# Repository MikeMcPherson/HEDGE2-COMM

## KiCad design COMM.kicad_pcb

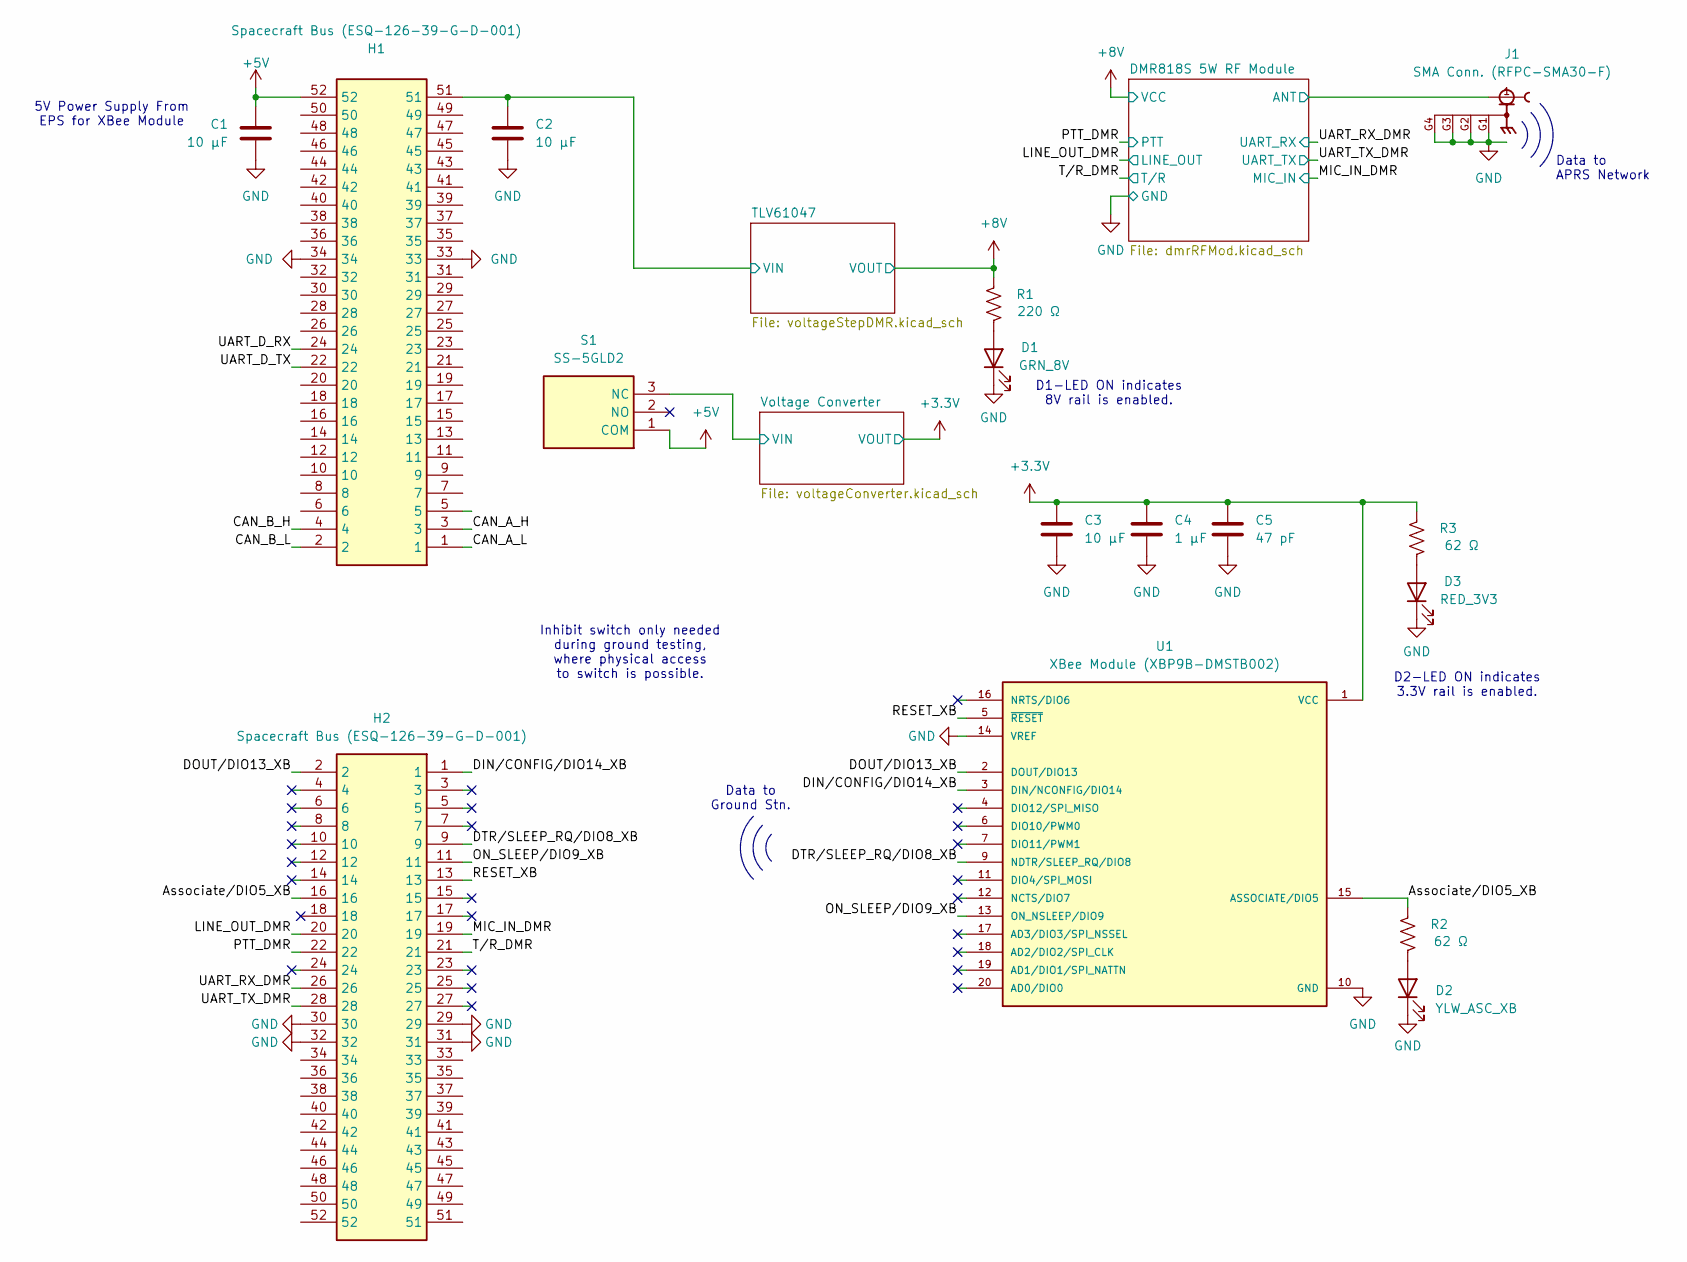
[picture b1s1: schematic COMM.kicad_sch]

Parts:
C1, C2, C3: 10 μF; CAPC1005X70N
C4: 1 μF; CAPC1005X55N
C5: 47 pF; CAPC1005X55N
D1: GRN_8V; LED_D5.0mm
D2: YLW_ASC_XB; LED_D5.0mm
D3: RED_3V3; LED_D5.0mm
H1, H2: Spacecraft Bus (ESQ-126-39-G-D-001); RHDR52W64P254_2X26_6654X495X1135P; Manufacturer_Part_Number ESQ-126-39-G-D-001; Mouser Part Number 200-ESQ12639GD001
J1: SMA Conn. (RFPC-SMA30-F); GRADCONN_RFPC-SMA30-F; PARTREV 1.0
R1: 220 Ω; R_0603_1608Metric
R2, R3: 62 Ω; R_0603_1608Metric
S1: SS-5GLD2; SS5GLD2; Manufacturer_Part_Number SS-5GLD2; Mouser Part Number 653-SS-5GLD2
U1: XBee Module (XBP9B-DMSTB002); DIP2200W51P200L3294H279Q20P

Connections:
+3.3V: C3.1, C4.1, C5.1, R3.2, U1.1 (VCC); also elsewhere on the board
+5V: C1.1, H1.52, S1.1 (COM)
+8V: R1.2; also elsewhere on the board
/Associate/DIO5_XB: H2.16, R2.2, U1.15 (ASSOCIATE/DIO5)
/CAN_A_H: H1.3
/CAN_A_L: H1.1
/CAN_B_H: H1.4
/CAN_B_L: H1.2
/DIN/CONFIG/DIO14_XB: H2.1, U1.3 (DIN/NCONFIG/DIO14)
/DMR818S 5W RF Module/ANT: J1.1; also elsewhere on the board
/DOUT/DIO13_XB: H2.2, U1.2 (DOUT/DIO13)
/DTR/SLEEP_RQ/DIO8_XB: H2.9, U1.9 (NDTR/SLEEP_RQ/DIO8)
/LINE_OUT_DMR: H2.20; also elsewhere on the board
/MIC_IN_DMR: H2.19; also elsewhere on the board
/ON_SLEEP/DIO9_XB: H2.11, U1.13 (ON_NSLEEP/DIO9)
/PTT_DMR: H2.22; also elsewhere on the board
/RESET_XB: H2.13, U1.5 (~RESET)
/TLV61047/VIN: C2.1, H1.51; also elsewhere on the board
/T/R_DMR: H2.21; also elsewhere on the board
/UART_D_RX: H1.24
/UART_D_TX: H1.22
/UART_RX_DMR: H2.26; also elsewhere on the board
/UART_TX_DMR: H2.28; also elsewhere on the board
/Voltage Converter/VIN: S1.3 (NC); also elsewhere on the board
GND: C1.2, C2.2, C3.2, C4.2, C5.2, D1.1 (K), D2.1 (K), D3.1 (K), H1.33, H1.34, H2.29, H2.30, H2.31, H2.32, J1.G1, J1.G2, J1.G3, J1.G4, U1.10 (GND), U1.14 (VREF); also elsewhere on the board
unnamed: D1.2 (A), R1.1
unnamed: D2.2 (A), R2.1
unnamed: D3.2 (A), R3.1

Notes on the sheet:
Data to APRS Network
Inhibit switch only needed during ground testing, where physical access to switch is possible.
5V Power Supply From EPS for XBee Module
Data to Ground Stn.
D1-LED ON indicates 8V rail is enabled.
D2-LED ON indicates 3.3V rail is enabled.

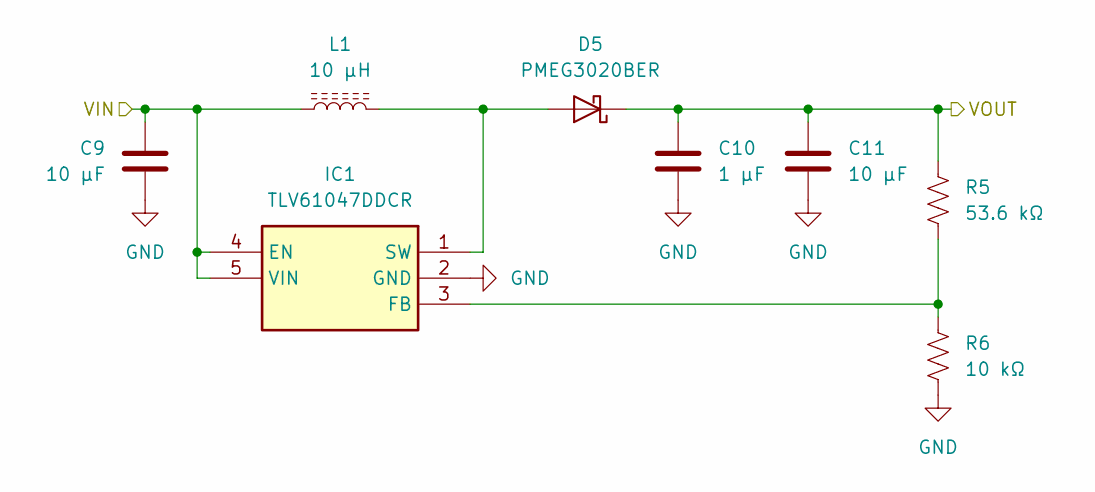
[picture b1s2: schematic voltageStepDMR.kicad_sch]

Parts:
C9, C11: 10 μF; CAPC1005X70N
C10: 1 μF; CAPC1005X55N
D5: PMEG3020BER; DIODE_SOD123W_1P9X2P8_NEX
IC1: TLV61047DDCR; SOT95P280X110-5N; Manufacturer_Part_Number TLV61047DDCR
L1: 10 μH; IND_XAL4040-103MEC
R5: 53.6 kΩ; RESC1608X55N
R6: 10 kΩ; RESC1005X40N

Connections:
+8V: C10.1, C11.1, D5.1 (K), R5.1; also elsewhere on the board
/TLV61047/VIN: C9.1, IC1.4 (EN), IC1.5 (VIN), L1.1; also elsewhere on the board
GND: C9.2, C10.2, C11.2, IC1.2 (GND), R6.2; also elsewhere on the board
unnamed: D5.2 (A), IC1.1 (SW), L1.2
unnamed: IC1.3 (FB), R5.2, R6.1

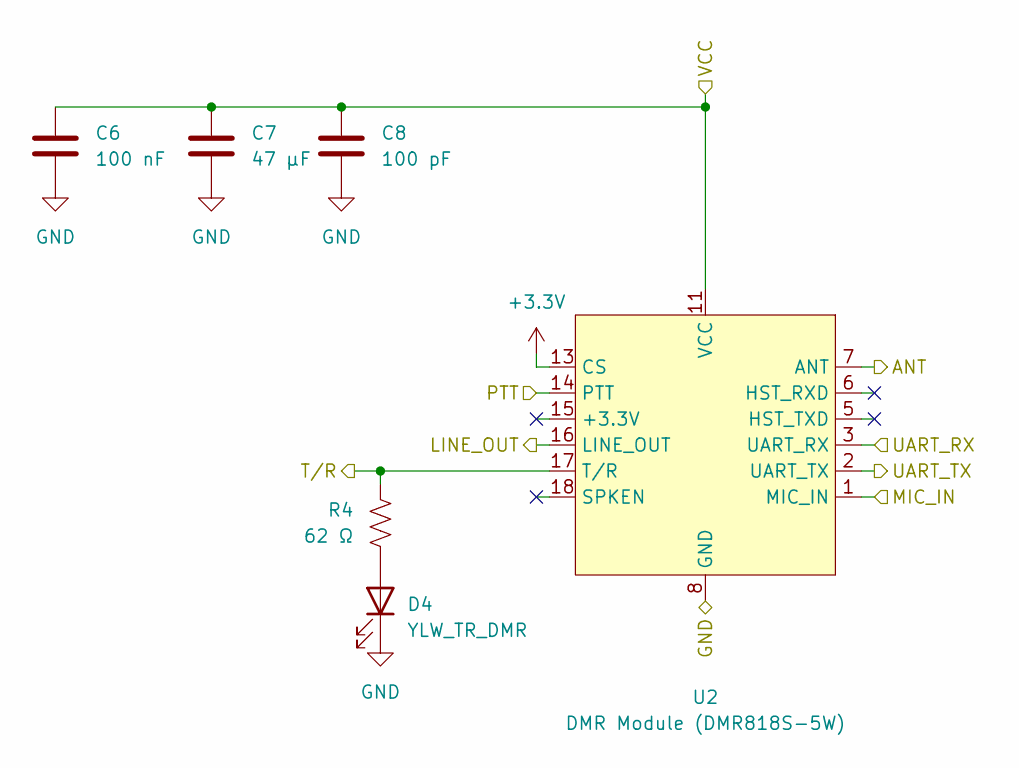
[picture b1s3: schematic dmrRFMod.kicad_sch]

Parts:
C6: 100 nF; CAPC1608X90
C7: 47 μF; CAPC2012X135N
C8: 100 pF; CAPC1005X55N
D4: YLW_TR_DMR; LED_D5.0mm
R4: 62 Ω; R_0603_1608Metric
U2: DMR Module (DMR818S-5W); DMR818S-5W

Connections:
+3.3V: U2.13 (CS); also elsewhere on the board
+8V: C6.1, C7.1, C8.1, U2.11 (VCC); also elsewhere on the board
/DMR818S 5W RF Module/ANT: U2.7 (ANT); also elsewhere on the board
/LINE_OUT_DMR: U2.16 (LINE_OUT); also elsewhere on the board
/MIC_IN_DMR: U2.1 (MIC_IN); also elsewhere on the board
/PTT_DMR: U2.14 (PTT); also elsewhere on the board
/T/R_DMR: R4.1, U2.17 (T/R); also elsewhere on the board
/UART_RX_DMR: U2.3 (UART_RX); also elsewhere on the board
/UART_TX_DMR: U2.2 (UART_TX); also elsewhere on the board
GND: C6.2, C7.2, C8.2, D4.1 (K), U2.8 (GND), U2.9 (GND), U2.10 (GND), U2.19 (GND), U2.20 (GND), U2.21 (GND); also elsewhere on the board
unnamed: D4.2 (A), R4.2

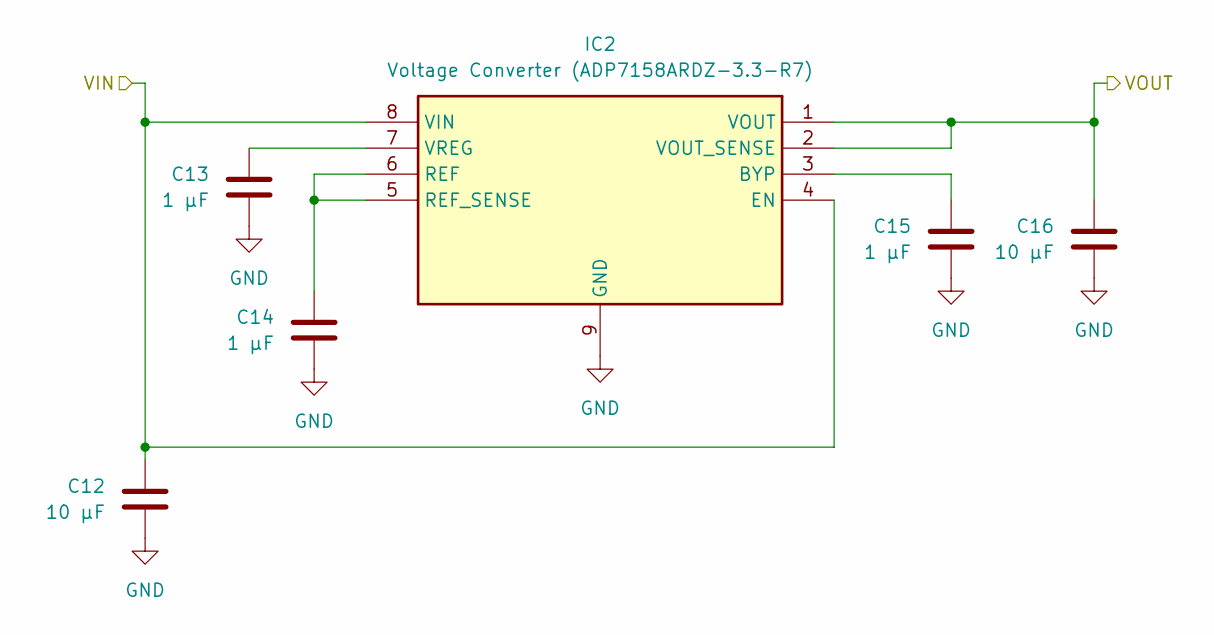
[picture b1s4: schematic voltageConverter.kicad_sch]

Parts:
C12, C16: 10 μF; CAPC1005X70N
C13, C14, C15: 1 μF; CAPC1005X55N
IC2: Voltage Converter (ADP7158ARDZ-3.3-R7); SOIC127P600X175-9N; Manufacturer_Part_Number ADP7158ARDZ-3.3-R7; Mouser Part Number 584-ADP7158ARDZ3.3R7

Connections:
+3.3V: C16.1, IC2.1 (VOUT), IC2.2 (VOUT_SENSE); also elsewhere on the board
/Voltage Converter/VIN: C12.1, IC2.4 (EN), IC2.8 (VIN); also elsewhere on the board
GND: C12.2, C13.2, C14.2, C15.2, C16.2, IC2.9 (GND); also elsewhere on the board
unnamed: C15.1, IC2.3 (BYP)
unnamed: C14.1, IC2.5 (REF_SENSE), IC2.6 (REF)
unnamed: C13.1, IC2.7 (VREG)

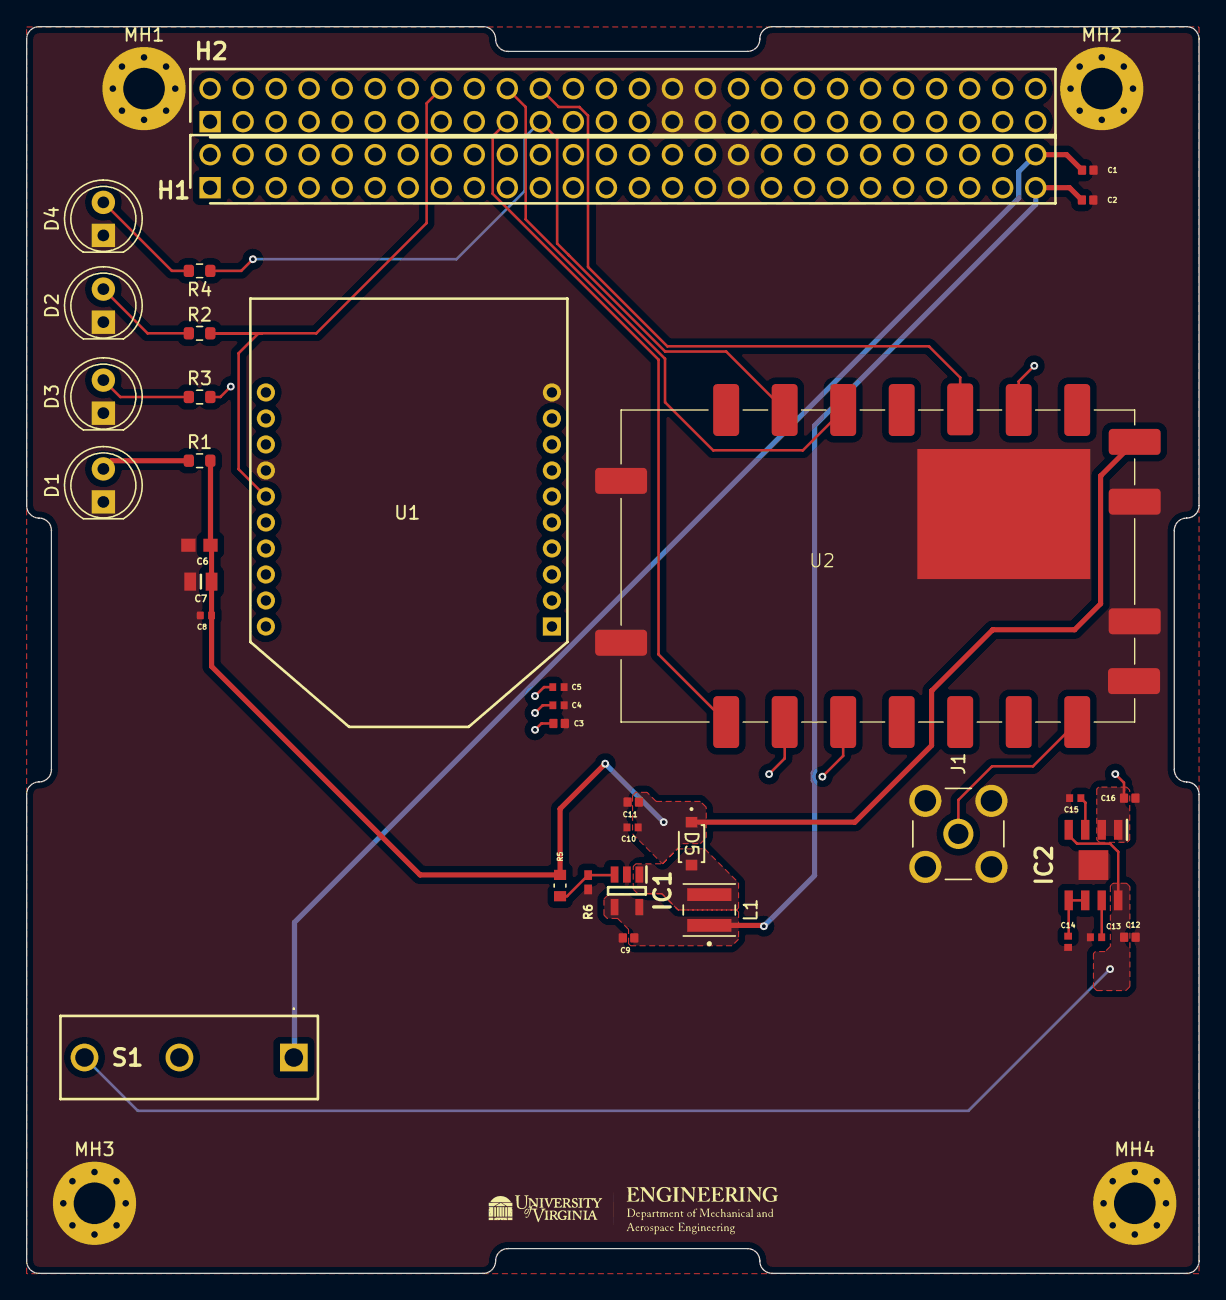
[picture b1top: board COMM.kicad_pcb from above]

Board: 4 copper layers, 90.2 x 95.9 mm, 40 parts (0 on the bottom side), 28 nets.

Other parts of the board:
MH1, MH2, MH3, MH4: MountingHole_Pad; MountingHole_3.2mm_M3_Pad_Via

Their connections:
GND: MH1.1, MH2.1, MH3.1, MH4.1; also elsewhere on the board

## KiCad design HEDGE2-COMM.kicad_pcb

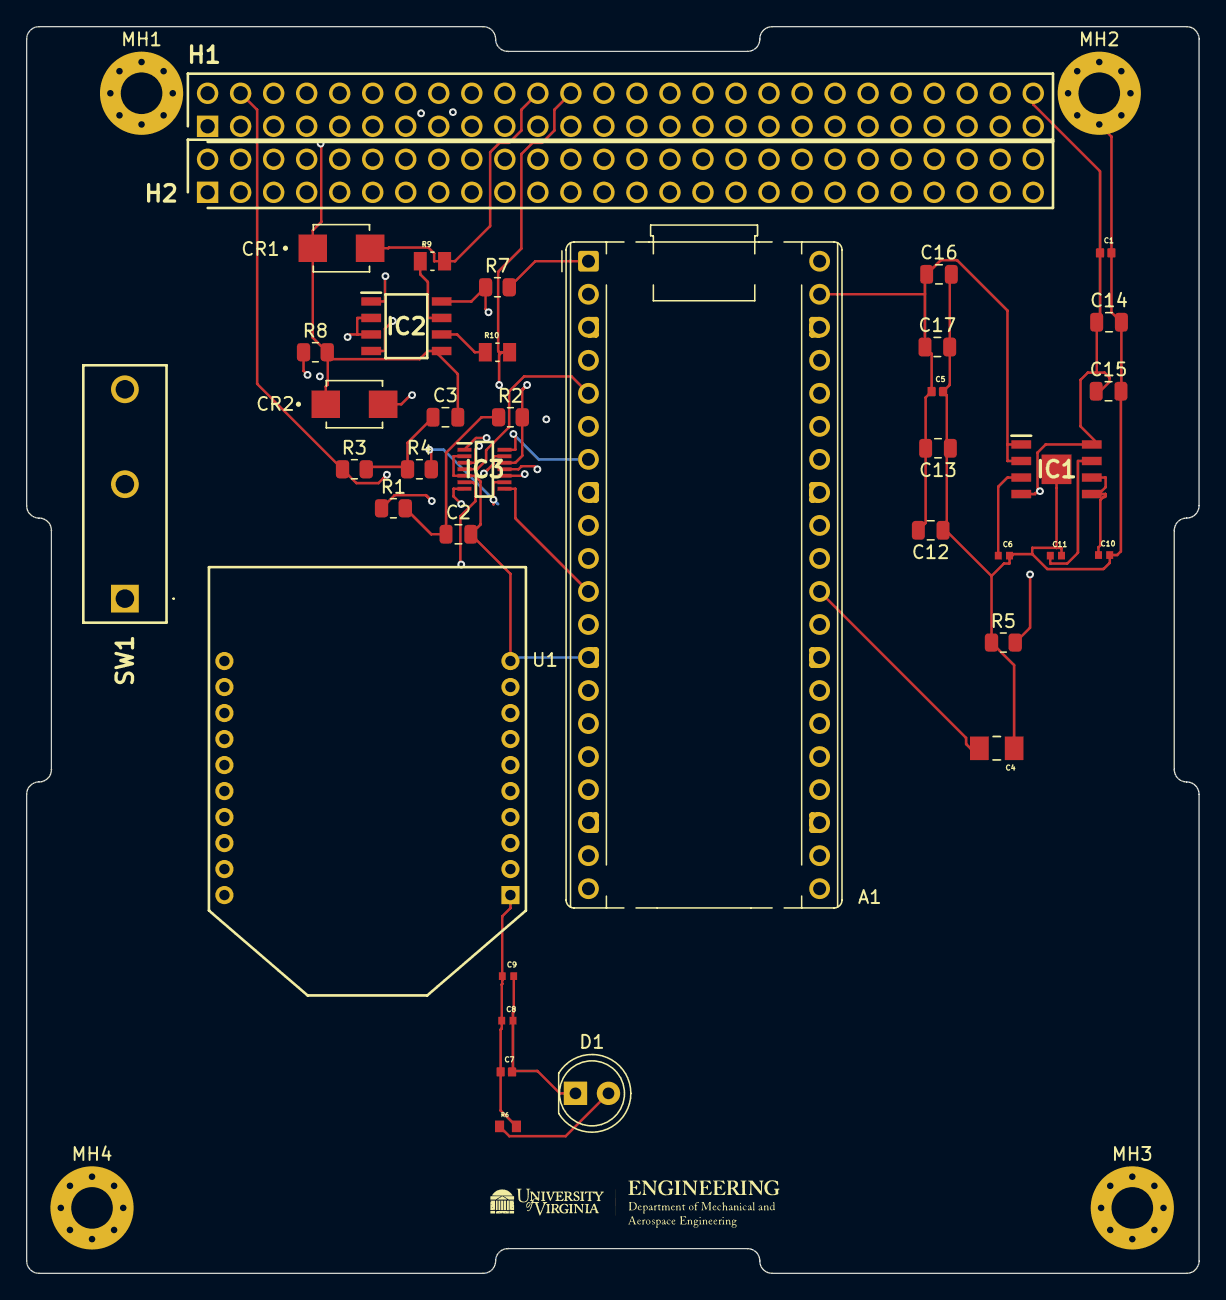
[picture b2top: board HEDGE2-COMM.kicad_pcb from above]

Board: 4 copper layers, 90.2 x 95.9 mm, 42 parts (0 on the bottom side), 35 nets.

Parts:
A1: RaspberryPi_Pico; RaspberryPi_Pico_Common_THT
C1, C5, C7: 10 μF; CAPC1005X70N
C2, C3, C15, C17: 0.1 μF; C_0805_2012Metric
C4: 33 µF; CAPC3216X180N
C6, C8, C10, C11: 1 μF; CAPC1005X55N
C9: 47 pF; CAPC1005X55N
C12, C13: 100 nF; C_0805_2012Metric
C14, C16: 4.7 μF; C_0805_2012Metric
CR1, CR2: SMBJ43CA; DIOM4336X265N
D1: LED; LED_D5.0mm
H1, H2: Spacecraft Bus (ESQ-126-39-G-D-001); RHDR52W64P254_2X26_6654X495X1135P
IC1: Voltage Converter (ADP7158ARDZ-3.3-R7); SOIC127P600X175-9N
IC2: SN65HVD1782QDRQ1; SOIC127P600X175-8N
IC3: TCAN1046AVDYYRQ1; SOP50P326X110-14N
MH1, MH2, MH3, MH4: MountingHole_Pad; MountingHole_3.2mm_M3_Pad_Via
R1, R2, R3, R4: 60 Ω; R_0805_2012Metric
R5: 300 Ω; R_0805_2012Metric
R6: 10Ω; RESC1005X40
R7, R8: 10 kΩ; R_0805_2012Metric
R9, R10: 10 Ω; RESC2012X65N
SW1: Inhibit Switch (SS5GLD2); SS5GLD2
U1: XBee Module (XBP9B-DMSTB002); DIP2200W51P200L3294H279Q20P

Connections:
+3.3V: A1.39 (VSYS), C5.1, C12.2, C13.2, C16.1, C17.1, IC1.1 (VOUT), IC1.2 (VOUT_SENSE), IC2.8 (VCC), IC3.11 (VIO), R7.1, SW1.1 (A)
+5V: C1.1, C14.1, C15.1, H1.52, IC1.4 (EN), IC1.8 (VIN), IC3.3 (VCC)
/CAN_A_H: H1.3, IC3.13 (CANH1), R1.1
/CAN_A_L: H1.1, IC3.12 (CANL1), R2.2
/CAN_A_RX: A1.5 (GPIO3), IC3.4 (RXD1)
/CAN_A_S: A1.7 (GPIO5), IC3.14 (STB1)
/CAN_A_TX: A1.6 (GPIO4), IC3.1 (TXD1)
/CAN_B_H: H1.4, IC3.10 (CANH2), R3.1
/CAN_B_L: H1.2, IC3.9 (CANL2), R4.2
/CAN_B_RX: A1.9 (GPIO6), IC3.7 (RXD2)
/CAN_B_S: A1.11 (GPIO8), IC3.8 (STB2)
/CAN_B_TX: A1.10 (GPIO7), IC3.6 (TXD2)
/GPIO_DIR: A1.4 (GPIO2), IC2.2 (RE), IC2.3 (DE), R8.1
/GPIO_IN: A1.1 (GPIO0), IC2.1 (R), R7.2
/GPIO_OUT: A1.2 (GPIO1), IC2.4 (D)
/UART_D_RX: CR2.2, H1.24, R10.2
/UART_D_TX: CR1.2, H1.22, R9.2
GND: A1.3 (GND), A1.8 (GND), A1.13 (GND), A1.18 (GND), A1.23 (GND), A1.28 (GND), A1.33 (AGND), A1.38 (GND), C1.2, C2.2, C3.2, C4.1, C5.2, C6.2, C7.2, C8.2, C9.2, C10.2, C11.2, C12.1, C13.1, C14.2, C15.2, C16.2, C17.2, CR1.1, CR2.1, D1.1 (K), H1.33, H1.34, H2.29, H2.30, H2.31, H2.32, IC1.9 (GND), IC2.5 (GND), IC3.2 (GND1), IC3.5 (GND2), MH1.1, MH2.1, MH3.1, MH4.1, R5.1, R8.2, U1.10 (GND), U1.14 (VREF)
unnamed: A1.36 (3V3), C7.1, C8.1, C9.1, R6.2, U1.1 (VCC)
unnamed: A1.30 (RUN), A1.37 (3V3_EN), C4.2, SW1.2 (B)
unnamed: A1.21 (GPIO16), U1.2 (DOUT/DIO13)
unnamed: A1.22 (GPIO17), U1.3 (DIN/NCONFIG/DIO14)
unnamed: A1.24 (GPIO18), U1.6 (DIO10/PWM0)
unnamed: A1.25 (GPIO19), U1.7 (DIO11/PWM1)
unnamed: A1.26 (GPIO20), U1.13 (ON_NSLEEP/DIO9)
unnamed: A1.29 (GPIO22), U1.15 (ASSOCIATE/DIO5)
unnamed: C2.1, R1.2, R2.1
unnamed: C3.1, R3.2, R4.1
unnamed: D1.2 (A), R6.1
unnamed: C6.1, IC1.3 (BYP)
unnamed: C10.1, IC1.5 (REF_SENSE), IC1.6 (REF)
unnamed: C11.1, IC1.7 (VREG)
unnamed: IC2.6 (A), R10.1
unnamed: IC2.7 (B), R9.1
unnamed: R5.2, SW1.3 (C)

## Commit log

2025-09-07 Add files
2025-12-05 COMM board as of 12/5/2025
2025-12-05 Updated COMM board
    Includes: Xbee, RPico, TCAN, RS485
    As of 12/5/2025
2026-01-13 Implemented COMM board dummy board design.
2026-01-27 Finished schematic and fully routed PCB.
2026-01-27 Added 3D models to all components except DMR module, need to make a 3D model for that one.
2026-01-29 removed extraneous connections to the XBee and DMR modules on schematic and PCB.
2026-01-29 Corrected DMR footprint and adjusted some routing.
2026-01-29 Added pull-up to CS pin on DMR module.
2026-01-30 Added STEP file for DMR818S 2W Module
2026-02-02 Addressed most comments from McPherson, modified schematic.
2026-02-05 Finalized board design, updated DMR module to DMR818S-5W exact dimensions, rerouted PCB according to McPherson's comments. Added TLV61047 5V to 8V booster module.
2026-02-05 Modified traces
2026-02-06 Removed extranous capacitors and resistors off of DMR module. Final Board Design, check one more time before ordering parts.
2026-02-06 Modified 5V trace from switch to voltage step-down module
2026-02-07 Added BOM and BOM generator python script
2026-02-12 Final COMM board design as of Feb 12 2026, ready to order.
2026-03-24 Swapped H1 and H2 spacebuses and rewired according to the swap.
2026-03-31 Updated COMM board to account for errors found during testing
2026-04-07 Updated LEDs and associated resistors on board. COMM board is ready to be reordered.
2026-04-09 Switched positions for SMA connector and voltage regulator.
